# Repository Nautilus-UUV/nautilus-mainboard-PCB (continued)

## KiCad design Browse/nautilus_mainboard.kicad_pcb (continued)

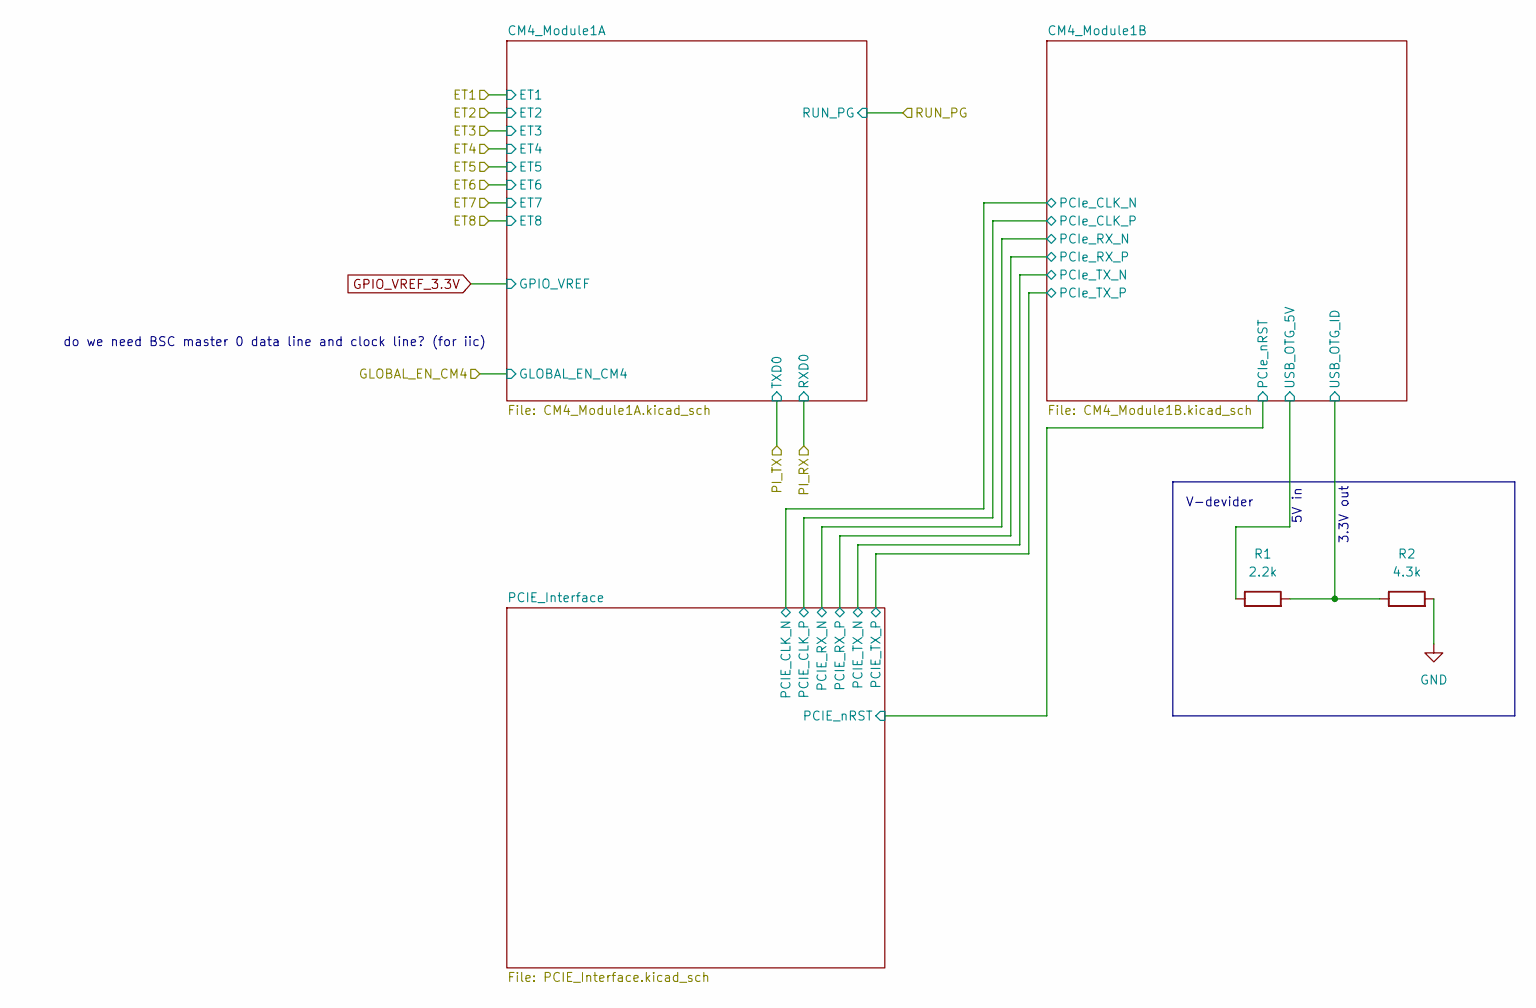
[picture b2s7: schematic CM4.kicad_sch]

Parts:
R1: 2.2k; R_0603_1608Metric; Tolerance 1 %; MPN 560112116098; LCSC CXXXXX
R2: 4.3k; R_0603_1608Metric; Tolerance 1 %; MPN 560112116141; LCSC CXXXXX

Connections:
/CM4/CM4_Module1B/USB_OTG_ID: R1.2, R2.1; also elsewhere on the board
GND: R2.2; also elsewhere on the board
USB_Out_5V: R1.1; also elsewhere on the board

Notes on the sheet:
do we need BSC master 0 data line and clock line? (for iic)
5V in
V-devider
3.3V out

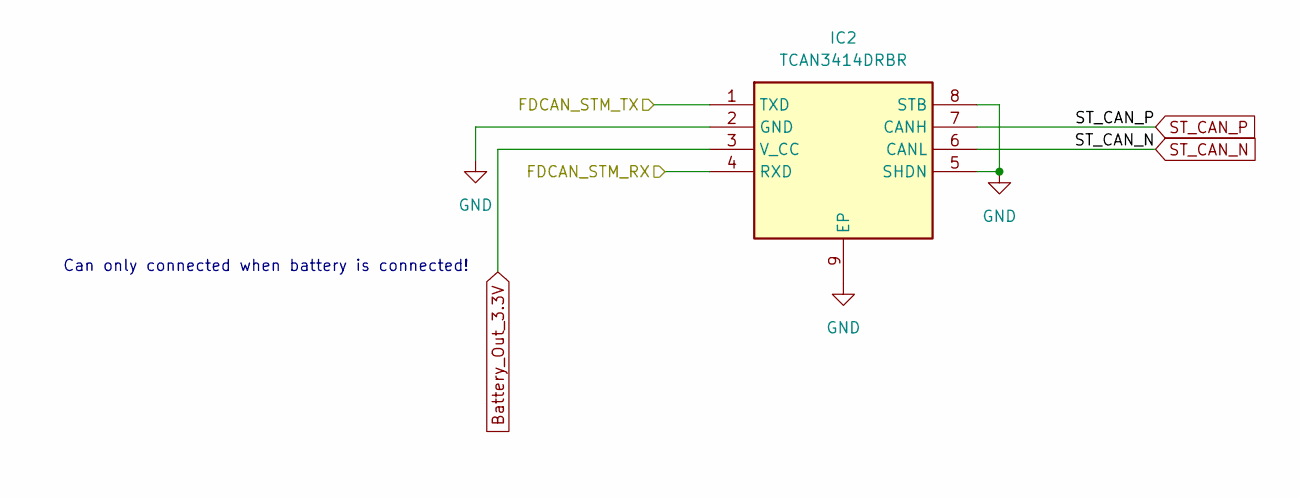
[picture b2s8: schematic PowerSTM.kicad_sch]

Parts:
IC2: TCAN3414DRBR; Mouser Part Number 595-TCAN3414DRBR

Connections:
/STM/PinoutSTM/CAN1_RX: IC2.4 (RXD); also elsewhere on the board
/STM/PinoutSTM/CAN1_TX: IC2.1 (TXD); also elsewhere on the board
GND: IC2.2 (GND), IC2.5 (SHDN), IC2.8 (STB), IC2.9 (EP); also elsewhere on the board
ST_CAN_N: IC2.6 (CANL); also elsewhere on the board
ST_CAN_P: IC2.7 (CANH); also elsewhere on the board

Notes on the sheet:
Can only connected when battery is connected!

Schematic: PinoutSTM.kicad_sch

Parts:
C8, C9: 4.7pF; C_0402_1005Metric; Voltage 50V; Tolerance ±0.25pF; MPN GRM1555C1H4R7CA01; LCSC C76946
C10, C15: 2.2pF; C_0402_1005Metric; Voltage 50V; Tolerance ±0.25pF; MPN GRM1555C1H2R2CA01; LCSC C85938
C11, C12, C13, C14, C17, C18, C19: 100nF; C_0603_1608Metric; Voltage 50V; Tolerance 10%; MPN 885012206095; LCSC CXXXXX
C16: 10uF; C_1210_3225Metric; Voltage 100V; Tolerance 10%; MPN GRM32EC72A106KE05; LCSC C5444485
EXTERNALFAN5V1: 0; R_0603_1608Metric; Tolerance 5%; MPN 560112116001; LCSC CXXXXX
IC1: STM32H7B0RBT6; LQFP-64_10x10mm_P0.5mm; Voltage 1.62V - 3.6V; Mouser Part Number 511-STM32H7B0RBT6
J1: FTSH-107-02-L-DV; FTSH-107-XX-YYY-DV; Mouser Part Number 200-FTSH10702LDV
J2: 61300211121; Wurth_Con_61300211121; MPN 61300211121
J4: Header male 1x05; PinHeader_1x05_P2.54mm_Vertical; MPN 22284054; LCSC C7501263
J5: 1792876; TerminalBlock_Phoenix_PT-1,5-3-5.0-H_1x03_P5.00mm_Horizontal; MPN 1792876; LCSC C976597
Q1: 50V; onsemi_Mosfet_BSS138; PARTREV 30 Jan 2018
R3: 1k; R_0603_1608Metric; Tolerance 1 %; MPN 560112116014; LCSC CXXXXX
R4: 10k; R_0603_1608Metric; Tolerance 1 %; MPN 560112116005; LCSC CXXXXX
SW1: Button Switch SPST-No; SW_PUSH_6mm; MPN B3F-1052; LCSC C87037
Y1: CC4V-T1A-32.768kHz-6pF-20PPM-TA-QC; CC4VT1A; Mouser Part Number 428-203148-MG02

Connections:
/CM4/CM4_Module1A/GPIO14: IC1.17 (PA3); also elsewhere on the board
/CM4/CM4_Module1A/GPIO15: IC1.16 (PA2); also elsewhere on the board
/CM4/GLOBAL_EN_CM4: IC1.11 (PC3); also elsewhere on the board
/CM4/RUN_PG: IC1.10 (PC2); also elsewhere on the board
/IMU/Pack1_SCL: IC1.61 (PB8); also elsewhere on the board
/IMU/Pack1_SDA: IC1.62 (PB9); also elsewhere on the board
/STM/PinoutSTM/CAN1_RX: IC1.43 (PA11); also elsewhere on the board
/STM/PinoutSTM/CAN1_TX: IC1.44 (PA12); also elsewhere on the board
/STM/PinoutSTM/Fan_ctrl: IC1.59 (PB7), R3.1
/STM/PinoutSTM/JTAG_ TDI: IC1.50 (PA15), J1.10
/STM/PinoutSTM/JTAG_TCK/SWCLK: IC1.49 (PA14), J1.6
/STM/PinoutSTM/JTAG_TDO/SWO: IC1.55 (PB3), J1.8
/STM/PinoutSTM/JTAG_TMS/SWDIO: IC1.45 (PA13), J1.4
/STM/PinoutSTM/SPI1_MISO: IC1.22 (PA6)
/STM/PinoutSTM/SPI1_MOSI: IC1.23 (PA7)
/STM/PinoutSTM/SPI1_NSS: IC1.20 (PA4)
/STM/PinoutSTM/SPI1_SCK: IC1.21 (PA5)
/STM/PinoutSTM/STM_BOOT0: IC1.60 (BOOT0), J4.4, R4.1
/STM/PinoutSTM/USART1_RX: IC1.42 (PA10), J1.13, J4.2
/STM/PinoutSTM/USART1_TX: IC1.41 (PA9), J1.14, J4.3
/STM/PinoutSTM/nRST: C19.1, IC1.7 (NRST), J1.12, SW1.1
BMI_IN_3.3V: C11.1, C12.1, C13.1, C14.1, C16.1, C17.1, C18.1, IC1.1 (VBAT), IC1.13 (VDDA), IC1.19 (VDD_1), IC1.32 (VDD_2), IC1.48 (VDD_3), IC1.64 (VDD_4), J1.3; also elsewhere on the board
Battery_Out_5V: EXTERNALFAN5V1.1, J5.1, J5.3; also elsewhere on the board
GND: C8.2, C9.2, C10.2, C11.2, C12.2, C13.2, C14.2, C15.2, C16.2, C17.2, C18.2, C19.2, IC1.12 (VSSA), IC1.18 (VSS_1), IC1.31 (VSS_2), IC1.47 (VSS_3), IC1.63 (VSS_4), J1.5, J1.7, J1.11, J2.2, J4.5, Q1.2, R4.2, SW1.2; also elsewhere on the board
unnamed: EXTERNALFAN5V1.2, J2.1
unnamed: C8.1, IC1.3 (PC14-OSC32_IN), Y1.2 (OUTPUT)
unnamed: C9.1, IC1.4 (PC15-OSC32_OUT), Y1.1
unnamed: C10.1, IC1.30 (VCAP_1)
unnamed: C15.1, IC1.46 (VCAP_2)
unnamed: J5.2, Q1.3
unnamed: Q1.1, R3.2
STM_Plug_3.3V: J4.1; also elsewhere on the board
STM_RX: IC1.15 (PA1); also elsewhere on the board
STM_TX: IC1.14 (PA0); also elsewhere on the board

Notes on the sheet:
Fan controller
I am a fan.
Connected to PB7
fan only active when battery is connected. Mby add an external power pin to externally power the fan for testing.
logic handled in power section
External interfaces
3v3 ext was first implemented here
- +

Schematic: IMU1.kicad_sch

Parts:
C43, C44: 100nF; C_0603_1608Metric; Voltage 50V; Tolerance 10%; MPN 885012206095; LCSC CXXXXX
R50, R51, R53: 0; R_0603_1608Metric; Tolerance 5%; MPN 560112116001; LCSC CXXXXX
U1: 262-BMI088; Bosch_IMU_BMI088; MPN 262-BMI088

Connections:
BMI_IN_3.3V: C43.2, C44.2, R53.1, U1.3 (VDD), U1.11 (VDDIO); also elsewhere on the board
GND: C43.1, C44.1, U1.2 (NC), U1.4 (GNDA), U1.6 (GNDIO), U1.10 (SDO2), U1.15 (SDO1); also elsewhere on the board
unnamed 130: R53.2, U1.7 (PS), U1.14 (CSB1); also elsewhere on the board
unnamed 131: R50.2, U1.8 (SCL/SCK); also elsewhere on the board
unnamed 132: R51.2, U1.9 (SDA/SDI); also elsewhere on the board

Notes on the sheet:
Accelerometer SD01 pin pulled to GND (0x18) SD01 pin pulled to VDDIO: (0x19) Gyroscope: SD02 pin pulled to GND: (0x68) SDO2 pin pulled to VDDIO: 0x69)
PB8 on STM
Acc: 0x18 Gyro: 0x68
PB9 on STM
PS -> 3.3V IIC CSB1 -> 3.3V NOT SPI

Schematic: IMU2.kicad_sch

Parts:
C45, C46: 100nF; C_0603_1608Metric; Voltage 50V; Tolerance 10%; MPN 885012206095; LCSC CXXXXX
R48, R49, R52: 0; R_0603_1608Metric; Tolerance 5%; MPN 560112116001; LCSC CXXXXX
U2: 262-BMI088; Bosch_IMU_BMI088; MPN 262-BMI088

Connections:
BMI_IN_3.3V: C45.2, C46.2, R52.1, U2.3 (VDD), U2.10 (SDO2), U2.11 (VDDIO), U2.15 (SDO1); also elsewhere on the board
GND: C45.1, C46.1, U2.2 (NC), U2.4 (GNDA), U2.6 (GNDIO); also elsewhere on the board
unnamed 133: R52.2, U2.7 (PS), U2.14 (CSB1); also elsewhere on the board
unnamed 134: R48.2, U2.8 (SCL/SCK); also elsewhere on the board
unnamed 135: R49.2, U2.9 (SDA/SDI); also elsewhere on the board

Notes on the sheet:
Acc: 0x19 Gyro: 0x69
PB8 on STM
PB9 on STM
Accelerometer SD01 pin pulled to GND (0x18) SD01 pin pulled to VDDIO: (0x19) Gyroscope: SD02 pin pulled to GND: (0x68) SDO2 pin pulled to VDDIO: 0x69)
PS -> 3.3V IIC CSB1 -> 3.3V NOT SPI

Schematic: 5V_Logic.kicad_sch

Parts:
C21, C22: 10uF; C_1210_3225Metric; Voltage 100V; Tolerance 10%; MPN GRM32EC72A106KE05; LCSC C5444485
C23, C24, C26: 100nF; C_0603_1608Metric; Voltage 50V; Tolerance 10%; MPN 885012206095; LCSC CXXXXX
C25: 330nF; C_0603_1608Metric; Voltage 50V; Tolerance 10%; MPN 885012206098; LCSC CXXXXX
C27: 47uF; C_0805_2012Metric; Voltage 10V; Tolerance 20%; MPN GRM21BR61A476ME15; LCSC C124129
IC3: TPS2121RUXT; TI_Switchover_TPS2121RUXT; Mouser Part Number 595-TPS2121RUXT
R16: 15.4k; R_0603_1608Metric; Tolerance 1 %; MPN 560112116105; LCSC CXXXXX
R17, R19: 4.99k; R_0603_1608Metric; Tolerance 1 %; MPN 560112116132; LCSC CXXXXX
R18: 22k; R_0603_1608Metric; Tolerance 1 %; MPN 560112116022; LCSC CXXXXX
R20: 20k; R_0603_1608Metric; Tolerance 1 %; MPN 560112116015; LCSC CXXXXX

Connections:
Battery_Out_5V: C21.1, C23.1, IC3.7 (IN1), R16.2; also elsewhere on the board
CM4_IN_5V: C26.1, C27.1, IC3.1 (OUT_1), IC3.8 (OUT_2); also elsewhere on the board
GND: C21.2, C22.2, C23.2, C24.2, C25.2, C26.2, C27.2, IC3.4 (OV2), IC3.5 (OV1), IC3.12 (GND), R17.1, R18.2, R19.1; also elsewhere on the board
unnamed: IC3.3 (CP2), R19.2, R20.1
unnamed: IC3.10 (ILIM), R18.1
unnamed: IC3.6 (PR1), R16.1, R17.2
unnamed: C25.1, IC3.11 (SS)
USB_Out_5V: C22.1, C24.1, IC3.2 (IN2), R20.2; also elsewhere on the board

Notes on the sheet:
for questions about wiring etc please consult the datasheet...
V-div to 1.2V when IN1 = 5V
if the USB-only cold start "disconnects" we can try to bump SS to 470nF instead of 330nF.
PR1 > CP2 -> IN1 has prio
100nF CLOSE
https://www.ti.com/lit/ds/symlink/tps2120.pdf?ts=1761678178328
V-div to 1V when IN2=5V
wrong caps. 100nf + 10myF

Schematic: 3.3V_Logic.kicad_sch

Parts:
C28, C29: 10uF; C_1210_3225Metric; Voltage 100V; Tolerance 10%; MPN GRM32EC72A106KE05; LCSC C5444485
C30, C31, C33: 100nF; C_0603_1608Metric; Voltage 50V; Tolerance 10%; MPN 885012206095; LCSC CXXXXX
C32: 330nF; C_0603_1608Metric; Voltage 50V; Tolerance 10%; MPN 885012206098; LCSC CXXXXX
C34: 47uF; C_0805_2012Metric; Voltage 10V; Tolerance 20%; MPN GRM21BR61A476ME15; LCSC C124129
IC5: TPS2121RUXT; TI_Switchover_TPS2121RUXT; Mouser Part Number 595-TPS2121RUXT
R21: 15.4k; R_0603_1608Metric; Tolerance 1 %; MPN 560112116105; LCSC CXXXXX
R22, R24: 4.99k; R_0603_1608Metric; Tolerance 1 %; MPN 560112116132; LCSC CXXXXX
R23: 68k; R_0603_1608Metric; Tolerance 1 %; MPN 560112116064; LCSC CXXXXX
R25: 20k; R_0603_1608Metric; Tolerance 1 %; MPN 560112116015; LCSC CXXXXX

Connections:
BMI_IN_3.3V: C33.1, C34.1, IC5.1 (OUT_1), IC5.8 (OUT_2); also elsewhere on the board
GND: C28.2, C29.2, C30.2, C31.2, C32.2, C33.2, C34.2, IC5.4 (OV2), IC5.5 (OV1), IC5.12 (GND), R22.1, R23.2, R24.1; also elsewhere on the board
unnamed: IC5.3 (CP2), R24.2, R25.1
unnamed: IC5.10 (ILIM), R23.1
unnamed: IC5.6 (PR1), R21.1, R22.2
unnamed: C32.1, IC5.11 (SS)
STM_Plug_3.3V: C29.1, C31.1, IC5.2 (IN2), R25.2; also elsewhere on the board

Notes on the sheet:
100nF CLOSE
V-div (same ratio as 5V)
if the USB-only cold start "disconnects" we can try to bump SS to 470nF instead of 330nF.
22 kΩ → ~4.55 A 39 kΩ → ~2.78 A 50 kΩ → ~2.25 A 56 kΩ → ~2.04 A 68 kΩ → ~1.72 A 100 kΩ → ~1.24 A
Pin 10: 68k leads to about 1.72A (should be enough for STM)
[R] = [kOhm] 65.2 / R^0.861
PR1 > CP2 -> IN1 has prio
SAME AS IN 5V

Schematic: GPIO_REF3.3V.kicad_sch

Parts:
C35, C36: 10uF; C_1210_3225Metric; Voltage 100V; Tolerance 10%; MPN GRM32EC72A106KE05; LCSC C5444485
C37, C38, C39, C40: 100nF; C_0603_1608Metric; Voltage 50V; Tolerance 10%; MPN 885012206095; LCSC CXXXXX
C41: 47uF; C_0805_2012Metric; Voltage 10V; Tolerance 20%; MPN GRM21BR61A476ME15; LCSC C124129
IC4: TPS2121RUXT; TI_Switchover_TPS2121RUXT; Mouser Part Number 595-TPS2121RUXT
R14: 15.4k; R_0603_1608Metric; Tolerance 1 %; MPN 560112116105; LCSC CXXXXX
R26, R28: 4.99k; R_0603_1608Metric; Tolerance 1 %; MPN 560112116132; LCSC CXXXXX
R27, R30: 100k; R_0603_1608Metric; Tolerance 1 %; MPN 560112116004; LCSC CXXXXX
R29: 20k; R_0603_1608Metric; Tolerance 1 %; MPN 560112116015; LCSC CXXXXX

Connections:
BMI_IN_3.3V: C35.1, C37.1, IC4.7 (IN1), R14.2; also elsewhere on the board
GND: C35.2, C36.2, C37.2, C38.2, C39.2, C40.2, C41.2, IC4.4 (OV2), IC4.5 (OV1), IC4.12 (GND), R26.1, R27.2, R28.1, R30.2; also elsewhere on the board
GPIO_VREF_3.3V: C40.1, C41.1, IC4.1 (OUT_1), IC4.8 (OUT_2), R30.1; also elsewhere on the board
unnamed: IC4.3 (CP2), R28.2, R29.1
unnamed: IC4.10 (ILIM), R27.1
unnamed: IC4.6 (PR1), R14.1, R26.2
unnamed: C39.1, IC4.11 (SS)

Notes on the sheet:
Pin SS (11): 100nF soft start cap more than enoug as virtually no load at all at vref
PR1 > CP2 -> IN1 has prio
[R] = [kOhm] 65.2 / R^0.861
100nF CLOSE
100kOhm pulldown so Vref is low if everything is off (not floating)
V-div (same ratio as 5V)
22 kΩ → ~4.55 A 39 kΩ → ~2.78 A 50 kΩ → ~2.25 A 56 kΩ → ~2.04 A 68 kΩ → ~1.72 A 100 kΩ → ~1.24 A
SAME AS IN 5V
Pin 10: 100kOhm leads to about 1.24A (absolute overkill)

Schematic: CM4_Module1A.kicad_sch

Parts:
C1, C2, C3, C4, C5, C6: 100nF; C_0603_1608Metric; Voltage 50V; Tolerance 10%; MPN 885012206095; LCSC CXXXXX
C7, C42: 1uF; C_0603_1608Metric; Voltage 50V; Tolerance 10%; MPN 885012206126; LCSC CXXXXX
C47: 10uF; C_1210_3225Metric; Voltage 100V; Tolerance 10%; MPN GRM32EC72A106KE05; LCSC C5444485
Module1: DF40C-100DS-0.4V(51); Con-Raspberry-Pi-4-Compute-Module; Part Description 100 Position Connector Receptacle, Cent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; LCSC lifecycle=Active; note=100-pin 0.4mm pi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
Q2: 50V; onsemi_Mosfet_BSS138; PARTREV 30 Jan 2018

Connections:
/CM4/CM4_Module1A/AIN0: Module1.96 (AnalogIP0)
/CM4/CM4_Module1A/AIN1: Module1.94 (AnalogIP1)
/CM4/CM4_Module1A/CM4_LED1/nPWR_LED: Module1.95 (nPI_LED_PWR); also elsewhere on the board
/CM4/CM4_Module1A/CM4_LED2/PI_nLED_Activity: Module1.21 (PI_nLED_Activity); also elsewhere on the board
/CM4/CM4_Module1A/ETH_LED_G: Module1.15 (Ethernet_nLED3(3.3v)); also elsewhere on the board
/CM4/CM4_Module1A/ETH_LED_Y: Module1.17 (Ethernet_nLED2(3.3v)); also elsewhere on the board
/CM4/CM4_Module1A/GLOBAL_EN: Module1.99 (Global_EN), Q2.3
/CM4/CM4_Module1A/GPIO2: Module1.58 (GPIO2)
/CM4/CM4_Module1A/GPIO3: Module1.56 (GPIO3)
/CM4/CM4_Module1A/GPIO4: Module1.54 (GPIO4)
/CM4/CM4_Module1A/GPIO5: Module1.34 (GPIO5)
/CM4/CM4_Module1A/GPIO6: Module1.30 (GPIO6)
/CM4/CM4_Module1A/GPIO7: Module1.37 (GPIO7)
/CM4/CM4_Module1A/GPIO8: Module1.39 (GPIO8)
/CM4/CM4_Module1A/GPIO9: Module1.40 (GPIO9)
/CM4/CM4_Module1A/GPIO10: Module1.44 (GPIO10)
/CM4/CM4_Module1A/GPIO11: Module1.38 (GPIO11)
/CM4/CM4_Module1A/GPIO12: Module1.31 (GPIO12)
/CM4/CM4_Module1A/GPIO13: Module1.28 (GPIO13)
/CM4/CM4_Module1A/GPIO14: Module1.55 (GPIO14); also elsewhere on the board
/CM4/CM4_Module1A/GPIO15: Module1.51 (GPIO15); also elsewhere on the board
/CM4/CM4_Module1A/GPIO16: Module1.29 (GPIO16)
/CM4/CM4_Module1A/GPIO17: Module1.50 (GPIO17)
/CM4/CM4_Module1A/GPIO18: Module1.49 (GPIO18)
/CM4/CM4_Module1A/GPIO19: Module1.26 (GPIO19)
/CM4/CM4_Module1A/GPIO20: Module1.27 (GPIO20)
/CM4/CM4_Module1A/GPIO21: Module1.25 (GPIO21)
/CM4/CM4_Module1A/GPIO22: Module1.46 (GPIO22)
/CM4/CM4_Module1A/GPIO23: Module1.47 (GPIO23)
/CM4/CM4_Module1A/GPIO24: Module1.45 (GPIO24)
/CM4/CM4_Module1A/GPIO25: Module1.41 (GPIO25)
/CM4/CM4_Module1A/GPIO26: Module1.24 (GPIO26)
/CM4/CM4_Module1A/GPIO27: Module1.48 (GPIO27)
/CM4/CM4_Module1A/TRD0_N: Module1.10 (Ethernet_Pair0_N); also elsewhere on the board
/CM4/CM4_Module1A/TRD0_P: Module1.12 (Ethernet_Pair0_P); also elsewhere on the board
/CM4/CM4_Module1A/TRD1_N: Module1.6 (Ethernet_Pair1_N); also elsewhere on the board
/CM4/CM4_Module1A/TRD1_P: Module1.4 (Ethernet_Pair1_P); also elsewhere on the board
/CM4/CM4_Module1A/TRD2_N: Module1.9 (Ethernet_Pair2_N); also elsewhere on the board
/CM4/CM4_Module1A/TRD2_P: Module1.11 (Ethernet_Pair2_P); also elsewhere on the board
/CM4/CM4_Module1A/TRD3_N: Module1.5 (Ethernet_Pair3_N); also elsewhere on the board
/CM4/CM4_Module1A/TRD3_P: Module1.3 (Ethernet_Pair3_P); also elsewhere on the board
/CM4/GLOBAL_EN_CM4: Q2.1; also elsewhere on the board
/CM4/RUN_PG: Module1.92 (RUN_PG); also elsewhere on the board
CM4_IN_5V: C1.1, C2.1, C3.1, C4.1, C5.1, C6.1, C7.1, C42.1, C47.1, Module1.77 (+5v_(Input)), Module1.79 (+5v_(Input)), Module1.81 (+5v_(Input)), Module1.83 (+5v_(Input)), Module1.85 (+5v_(Input)), Module1.87 (+5v_(Input)); also elsewhere on the board
GND: C1.2, C2.2, C3.2, C4.2, C5.2, C6.2, C7.2, C42.2, C47.2, Module1.1 (GND), Module1.2 (GND), Module1.7 (GND), Module1.8 (GND), Module1.13 (GND), Module1.14 (GND), Module1.22 (GND), Module1.23 (GND), Module1.32 (GND), Module1.33 (GND), Module1.42 (GND), Module1.43 (GND), Module1.52 (GND), Module1.53 (GND), Module1.59 (GND), Module1.60 (GND), Module1.65 (GND), Module1.66 (GND), Module1.71 (GND), Module1.74 (GND), Module1.89 (WL_nDisable), Module1.91 (BT_nDisable), Module1.98 (GND), Q2.2; also elsewhere on the board
GPIO_VREF_3.3V: Module1.78 (GPIO_VREF(1.8v/3.3v_Input)); also elsewhere on the board

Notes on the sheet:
Ethernet connection
GLOBAL_EN logic
Decoupling for CM4 5V inputs
N/A
connect Wlan to gnd if off, and leave floating for on. Please use a 2 pin connector here with a jumper cap. (has to be done)
GLOBAL_EN needs to be pulled low for >1ms after software shutdown.
Disable Wlan and Bluetooth?

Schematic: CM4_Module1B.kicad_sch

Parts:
C20: 4.7nF; C_0603_1608Metric; Voltage 50V; Tolerance 10%; MPN 885012206087; LCSC CXXXXX
D5: APHHS1005LCGCK; LED_0402_1005Metric; MPN APHHS1005LCGCK; LCSC C5354975
D6: SMF5.0A-TP; SMF50ATP; MPN 833-SMF5.0A-TP
J18: 179-UJ20CHC4SMTTR; CON_Samesky_CUI_UJ20-C-H-C-4-SMT-TR; PARTREV 1.0
Module1: DF40C-100DS-0.4V(51); Con-Raspberry-Pi-4-Compute-Module; Part Description 100 Position Connector Receptacle, Cent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; LCSC lifecycle=Active; note=100-pin 0.4mm pi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
R9: 2.7k; R_0603_1608Metric; Tolerance 1 %; MPN 560112116010; LCSC CXXXXX
R10, R12: 4.99k; R_0603_1608Metric; Tolerance 1 %; MPN 560112116132; LCSC CXXXXX
R11: 1M; R_0603_1608Metric; Tolerance 1 %; MPN 560112116074; LCSC CXXXXX
TPD4EUSB30DQAR3: IC_TPD4EUSB30DQAR; PARTREV F; LCSC C90627

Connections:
/CM4/CM4_Module1B/PCIe_CLK_N: Module1.112 (PCIe_CLK_N); also elsewhere on the board
/CM4/CM4_Module1B/PCIe_CLK_P: Module1.110 (PCIe_CLK_P); also elsewhere on the board
/CM4/CM4_Module1B/PCIe_RX_N: Module1.118 (PCIe_RX_N); also elsewhere on the board
/CM4/CM4_Module1B/PCIe_RX_P: Module1.116 (PCIe_RX_P); also elsewhere on the board
/CM4/CM4_Module1B/PCIe_TX_N: Module1.124 (PCIe_TX_N); also elsewhere on the board
/CM4/CM4_Module1B/PCIe_TX_P: Module1.122 (PCIe_TX_P); also elsewhere on the board
/CM4/CM4_Module1B/USB_D+: J18.A6 (DP1), J18.B6 (DP2), Module1.105 (USB2_P), TPD4EUSB30DQAR3.1, TPD4EUSB30DQAR3.2, TPD4EUSB30DQAR3.9 (Through_2), TPD4EUSB30DQAR3.10 (Through_1)
/CM4/CM4_Module1B/USB_D-: J18.A7 (DN1), J18.B7 (DN2), Module1.103 (USB2_N), TPD4EUSB30DQAR3.4, TPD4EUSB30DQAR3.5, TPD4EUSB30DQAR3.6 (Through_5), TPD4EUSB30DQAR3.7 (Through_4)
/CM4/CM4_Module1B/USB_OTG_ID: Module1.101 (USB_OTG_ID); also elsewhere on the board
/CM4/PCIE_Interface/PERST#: Module1.109 (PCIe_nRST); also elsewhere on the board
GND: C20.1, D6.2 (A), J18.A1_B12 (GND), J18.A12_B1 (GND), Module1.107 (GND), Module1.108 (GND), Module1.113 (GND), Module1.114 (GND), Module1.119 (GND), Module1.120 (GND), Module1.125 (GND), Module1.126 (GND), Module1.131 (GND), Module1.132 (GND), Module1.137 (GND), Module1.138 (GND), Module1.144 (GND), Module1.150 (GND), Module1.155 (GND), Module1.156 (GND), Module1.161 (GND), Module1.162 (GND), Module1.167 (GND), Module1.168 (GND), Module1.173 (GND), Module1.174 (GND), Module1.179 (GND), Module1.180 (GND), Module1.185 (GND), Module1.186 (GND), Module1.191 (GND), Module1.192 (GND), Module1.197 (GND), Module1.198 (GND), R9.2, R10.2, R11.2, R12.2, TPD4EUSB30DQAR3.3, TPD4EUSB30DQAR3.8; also elsewhere on the board
unnamed: C20.2, J18.SH1 (SHIELD), J18.SH2 (SHIELD), J18.SH3 (SHIELD), J18.SH4 (SHIELD), R11.1
unnamed: D5.1 (K), R9.1
unnamed: J18.A5 (CC1), R10.1
unnamed: J18.B5 (CC2), R12.1
USB_Out_5V: D5.2 (A), D6.1 (K), J18.A4_B9 (VBUS), J18.A9_B4 (VBUS); also elsewhere on the board

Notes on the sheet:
ESD/EMP protection for the USB
USB Connection for CM4
old usb port for reference.
Can be kept floating. if no usb is connected
reduce EMI
maybe RX and TX need to be switched
indicator LED :)
WIP, nRPI_BOOT? power only to certain parts? -> Diode (later) indication? (YES! LED)
Super important to not differ lengths or curve a lot with D+ and D-. Also should have same hole counts (vias) and same length.

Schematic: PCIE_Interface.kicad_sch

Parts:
CONFIG_1, CONFIG_2, CONFIG_3, CONFIG_4: 0; R_0603_1608Metric; Tolerance 5%; MPN 560112116001; LCSC CXXXXX
D8: APHHS1005LCGCK; LED_0402_1005Metric; MPN APHHS1005LCGCK; LCSC C5354975
J6: MDT275M02001; PCIE_MDT275M02001; Mouser Part Number 523-MDT275M02001
R13: 1k; R_0603_1608Metric; Tolerance 1 %; MPN 560112116014; LCSC CXXXXX

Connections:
/CM4/CM4_Module1B/PCIe_CLK_N: J6.53; also elsewhere on the board
/CM4/CM4_Module1B/PCIe_CLK_P: J6.55; also elsewhere on the board
/CM4/CM4_Module1B/PCIe_RX_N: J6.41; also elsewhere on the board
/CM4/CM4_Module1B/PCIe_RX_P: J6.43; also elsewhere on the board
/CM4/CM4_Module1B/PCIe_TX_N: J6.47; also elsewhere on the board
/CM4/CM4_Module1B/PCIe_TX_P: J6.49; also elsewhere on the board
/CM4/PCIE_Interface/CLKREQ#: J6.52
/CM4/PCIE_Interface/CONFIG_0: CONFIG_1.2, J6.21
/CM4/PCIE_Interface/CONFIG_1: CONFIG_2.2, J6.69
/CM4/PCIE_Interface/CONFIG_2: CONFIG_3.2, J6.75
/CM4/PCIE_Interface/CONFIG_3: CONFIG_4.2, J6.1
/CM4/PCIE_Interface/LED1_M2: D8.2 (A), J6.10, R13.1
/CM4/PCIE_Interface/NFG1: J6.56
/CM4/PCIE_Interface/NFG2: J6.58
/CM4/PCIE_Interface/PERST#: J6.50; also elsewhere on the board
/CM4/PCIE_Interface/PERn1: J6.29
/CM4/PCIE_Interface/PERn2: J6.17
/CM4/PCIE_Interface/PERn3: J6.5
/CM4/PCIE_Interface/PERp1: J6.31
/CM4/PCIE_Interface/PERp2: J6.19
/CM4/PCIE_Interface/PERp3: J6.7
/CM4/PCIE_Interface/PETn1: J6.35
/CM4/PCIE_Interface/PETn2: J6.23
/CM4/PCIE_Interface/PETn3: J6.11
/CM4/PCIE_Interface/PETp1: J6.37
/CM4/PCIE_Interface/PETp2: J6.25
/CM4/PCIE_Interface/PETp3: J6.13
/CM4/PCIE_Interface/PEWAKE#: J6.54
/CM4/PCIE_Interface/SUSCLK: J6.68
GND: CONFIG_1.1, CONFIG_2.1, CONFIG_3.1, CONFIG_4.1, D8.1 (K), J6.3, J6.9, J6.15, J6.27, J6.33, J6.39, J6.45, J6.51, J6.57, J6.71, J6.73, J6.76 (MP_1), J6.77 (MP_2); also elsewhere on the board

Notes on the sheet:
Led indicator

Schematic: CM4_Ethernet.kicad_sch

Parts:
D3: APHHS1005LSYCK/J3-PF; LED_0402_1005Metric; MPN APHHS1005LSYCK/J3-PF; LCSC C5354974
D4: APHHS1005LZGCK-V; LED_0402_1005Metric; MPN APHHS1005LZGCK-V; LCSC C5875752
R7, R8: 1k; R_0603_1608Metric; Tolerance 1 %; MPN 560112116014; LCSC CXXXXX
TPD4EUSB30DQAR1, TPD4EUSB30DQAR2: IC_TPD4EUSB30DQAR; PARTREV F; LCSC C90627

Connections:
/CM4/CM4_Module1A/ETH_LED_G: D4.1 (K); also elsewhere on the board
/CM4/CM4_Module1A/ETH_LED_Y: D3.1 (K); also elsewhere on the board
/CM4/CM4_Module1A/TRD0_N: TPD4EUSB30DQAR2.2, TPD4EUSB30DQAR2.9 (Through_2); also elsewhere on the board
/CM4/CM4_Module1A/TRD0_P: TPD4EUSB30DQAR2.1, TPD4EUSB30DQAR2.10 (Through_1); also elsewhere on the board
/CM4/CM4_Module1A/TRD1_N: TPD4EUSB30DQAR2.4, TPD4EUSB30DQAR2.7 (Through_4); also elsewhere on the board
/CM4/CM4_Module1A/TRD1_P: TPD4EUSB30DQAR2.5, TPD4EUSB30DQAR2.6 (Through_5); also elsewhere on the board
/CM4/CM4_Module1A/TRD2_N: TPD4EUSB30DQAR1.2, TPD4EUSB30DQAR1.9 (Through_2); also elsewhere on the board
/CM4/CM4_Module1A/TRD2_P: TPD4EUSB30DQAR1.1, TPD4EUSB30DQAR1.10 (Through_1); also elsewhere on the board
/CM4/CM4_Module1A/TRD3_N: TPD4EUSB30DQAR1.4, TPD4EUSB30DQAR1.7 (Through_4); also elsewhere on the board
/CM4/CM4_Module1A/TRD3_P: TPD4EUSB30DQAR1.5, TPD4EUSB30DQAR1.6 (Through_5); also elsewhere on the board
GND: TPD4EUSB30DQAR1.3, TPD4EUSB30DQAR1.8, TPD4EUSB30DQAR2.3, TPD4EUSB30DQAR2.8; also elsewhere on the board
unnamed: D3.2 (A), R8.1
unnamed: D4.2 (A), R7.1

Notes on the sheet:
Optimal: Yellow: 725 Ohm (3.3-1.85)/0.002
POE Protection
Optimal: Green: 325 Ohm (3.3-2.65)/0.002

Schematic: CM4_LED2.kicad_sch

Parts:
D2: APHHS1005LZGCK-V; LED_0402_1005Metric; MPN APHHS1005LZGCK-V; LCSC C5875752
R6: 1k; R_0603_1608Metric; Tolerance 1 %; MPN 560112116014; LCSC CXXXXX

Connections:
/CM4/CM4_Module1A/CM4_LED2/PI_nLED_Activity: R6.1; also elsewhere on the board
unnamed: D2.1 (K), R6.2

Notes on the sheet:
Simple Activity LED
Activity LED

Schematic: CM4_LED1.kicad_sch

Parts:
D1: APHHS1005LSECK/J3-PF; LED_0402_1005Metric; MPN APHHS1005LSECK/J3-PF
R5: 1k; R_0603_1608Metric; Tolerance 1 %; MPN 560112116014; LCSC CXXXXX
U3: Buffers & Line Driver; SOT65P210X110-5N; MPN 74LVC1G07SE-7; LCSC C67531

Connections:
/CM4/CM4_Module1A/CM4_LED1/nPWR_LED: U3.2; also elsewhere on the board
GND: U3.3 (GND); also elsewhere on the board
unnamed 100: D1.1 (K), R5.2; also elsewhere on the board
unnamed: R5.1, U3.4

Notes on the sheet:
Directly copied from the official CM4 io board (indicator LED for 3.3v)
then I would in theory compare internal voltage with internal voltage... so probably not...
only use when connected completely? not over usb???
<---
issue: will that logic work if I use USB vin only?

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
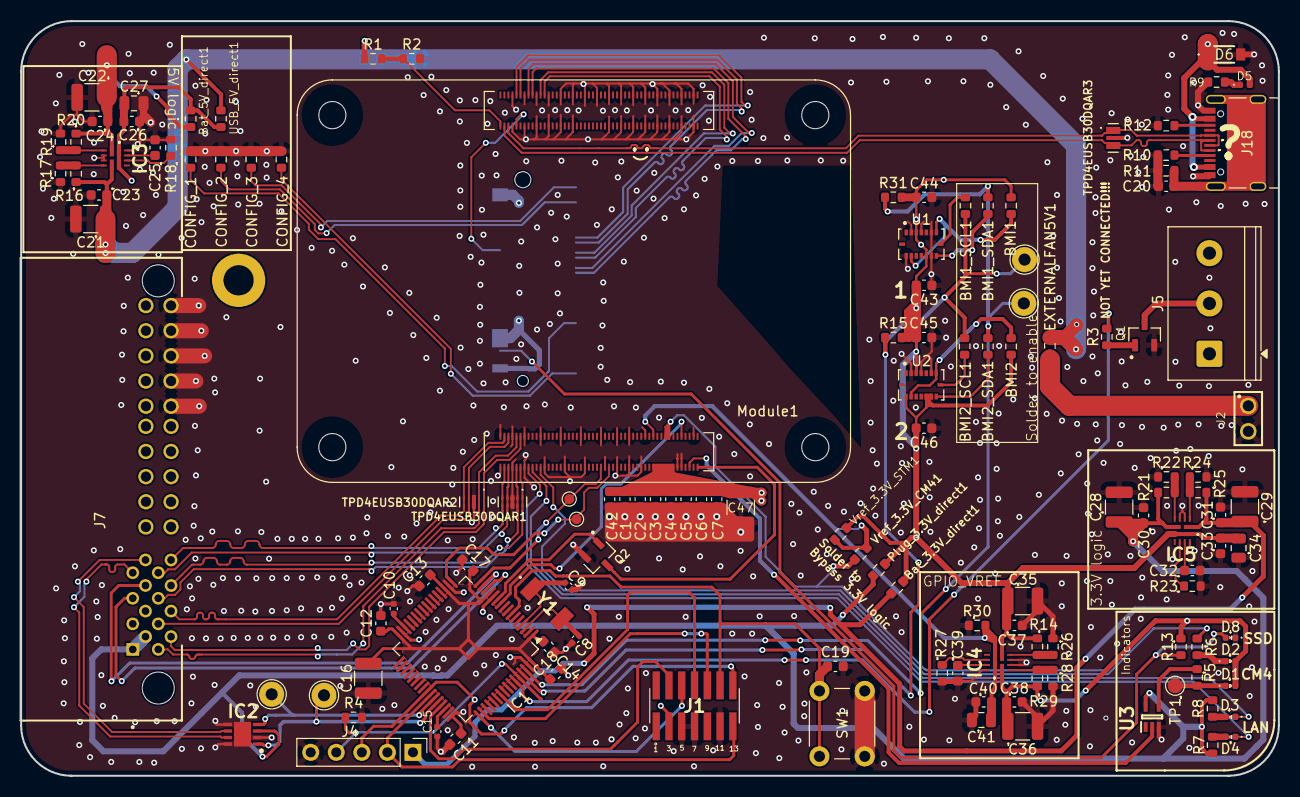
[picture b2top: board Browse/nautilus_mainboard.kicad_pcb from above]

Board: 4 copper layers, 125.0 x 75.0 mm, 132 parts (1 on the bottom side), 92 nets.

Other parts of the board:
BMI1, BMI1_SCL1, BMI1_SDA1, BMI2, BMI2_SCL1, BMI2_SDA1: 0; R_0603_1608Metric
TP1: Test Point; TestPoint_Pad_D1.5mm

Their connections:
/IMU/Pack1_SCL: BMI1_SCL1.1, BMI2_SCL1.1; also elsewhere on the board
/IMU/Pack1_SDA: BMI1_SDA1.1, BMI2_SDA1.1; also elsewhere on the board
BMI_IN_3.3V: BMI1.1, BMI2.1; also elsewhere on the board
unnamed 100: TP1.1; also elsewhere on the board
unnamed 130: BMI1.2; also elsewhere on the board
unnamed 131: BMI1_SCL1.2; also elsewhere on the board
unnamed 132: BMI1_SDA1.2; also elsewhere on the board
unnamed 133: BMI2.2; also elsewhere on the board
unnamed 134: BMI2_SCL1.2; also elsewhere on the board
unnamed 135: BMI2_SDA1.2; also elsewhere on the board

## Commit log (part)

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2025-09-19 Init
2025-09-20 test
2025-09-23 23.09.2025
2025-09-23 New Parts folder created, Additional pages for RTC created
2025-09-23 deleted backups and implemented gitignore
2025-10-14 Init2
2025-10-14 Added Indicator LED to CM4
2025-10-14 added gitignore, and did work on CM4
2025-10-15 started with the new STM integration
2025-10-16 Added other LED indicators, ethernet and connector (main connector to other pcb's)
2025-10-17 readded RX and TX, Corrected DZ_PATHS to be relative instead of absolute.
2025-10-17 Added usb connector
2025-10-18 added hirarchical pin
2025-10-18 Comments (+ new Connector?)
2025-10-21 Changed template of the sheet
2025-10-21 External interfaces
2025-10-21 WIFI connection changes PI
2025-10-21 beautyfie
2025-10-21 resolve project breaking merge conflict miss
2025-10-21 nothing
2025-10-21 Connected the Uart lines
2025-10-21 Implemented the entire can tranciever
2025-10-22 added more support for the ssd and fixed LED configuration
2025-10-26 multiple changes. fixed some mistakes, added jumper pins for wifi
2025-10-28 connector changes
2025-10-28 not working power distribution
2025-10-28 added caps
2025-10-28 power led
2025-10-28 added comment boxes
2025-10-28 simple changes
2025-10-28 scrivano datei (my thoughts written out)
2025-10-28 added fan Mosfet
2025-10-28 Added Power logic finally. (plus some comments on further improvements)
2025-10-29 tried to find some placements for power routing
2025-10-30 some PCB thoughts
2025-11-01 swapped vref and logic position
2025-11-01 checked the whole schematic with the datasheet, took notes/questions in the datasheet (pdf also uploaded)
2025-11-02 multiple changes to the differential pair for easier routing later.
2025-11-03 added Gyroscope and Accelerometer part (4x) over IIC
2025-11-04 connector with ssd
2025-11-04 new outline of board plus first traces
2025-11-04 ignore
2025-11-04 first tries with signal tracks
2025-11-10 routed the CAN
2025-11-10 fixed the can tranciever placement
2025-11-10 updated some diff pairs to be nicer
2025-11-10 cleaned up some schematic problems
2025-11-11 multiple chainges on PCB
2025-11-12 feat: kibot minimal setup
2025-11-12 fix: test easier config
2025-11-12 fix: run but don't fail on erc violations
2025-11-12 fix: check docs (https://kibot.readthedocs.io/en/latest/configuration/preflights/erc.html
2025-11-12 fix: disable checks
2025-11-12 fix: bump to kibot v2_k9
2025-11-12 feat: manual trigger
2025-11-12 fix: remove manual trigger, trigger on workflow change instead
2025-11-12 fix: use github maintained github action
2025-11-12 fix: make deploy separate job
2025-11-12 feat: test workflows from https://github.com/INTI-CMNB/kibot_variants_arduprog
2025-11-12 fix: revert to config workflow
2025-11-12 feat: improve to geenral config
2025-11-12 fix: keep running even on fail of ERC/DRC check
2025-11-12 fix: minimal config
2025-11-12 feat: add caching, fix: mkdir dir for Jekyll
2025-11-12 fix: race condition
2025-11-12 fix: removed unused files from the beginning (New_added_parts folder)
2025-11-12 feat: added README.md
2025-11-12 feat: go back to https://github.com/INTI-CMNB/kibot_variants_arduprog/blob/master/.github/workflows/kibot_quick_start.yml
2025-11-12 fix: add permission for private repo
2025-11-12 fix: add action: write permission
2025-11-12 chore: limit for quicker testing
2025-11-12 fix: specifically pass github_token
2025-11-13 fix: add pat token with permissions
2025-11-13 fix: no metadata permission exists
2025-11-13 fix: forgot to change PAT
2025-11-13 fix: add more outputs
2025-11-13 chore: for future uses of config, add index.html
2025-11-13 fix: try --quick-start with -D flag
2025-11-13 fix: just kibot --quick-start
2025-11-15 multiple rearrangements of the PCB
2025-11-15 feat: added multiple new routes to the PCB
2025-11-15 feat: new decoupling for STM chore: rethink the decoupling strategy for STM module (imo wayy too small)
2025-11-15 feat: nearly all connections done
2025-11-15 nearly complete with the PCB
2025-11-15 no substantial changes
2025-11-16 fix: widened the power tracks for 5V line
2025-11-16 added piezzo circuit and i2c line
2025-11-16 fix: adjusted copper to hole distance from 0.25mm to 0.2mm in order to meet the USB-C tolerances needed to use it.
2025-11-16 tented the vias(gnd) and routed the i2c and fan control path
2025-11-16 chore: remove DRC for pads being too close, or find a solution
2025-11-16 removed unused parts (piezzo) form pcb
2025-11-16 fix: adjusted clearance in order to pass DRC checks for BMI088
2025-11-16 chore: added a comment that piezzo buzzer wont be implemented right now
2025-11-16 chore: removed old hirarchical lables that were not being used anymore
2025-11-16 init with PDF
2025-11-16 fix: select types
2025-11-16 fix: removed ERC warnings, added missing overrides for ERC. Removed RX/TX for CM4, removed old power logic that was just there for legacy reasons.
2025-11-17 fix: remove token, repo public
2025-11-17 fix: test bare kibot --quick-start again
2025-11-17 fix: try -t navigate_results -t navigate_results_rb
2025-11-17 fix: cp nvigate page to index.html in root
2025-11-17 feat: generate index.html, add kikit_present
2025-11-17 fix: add navigation_results
2025-11-17 feat: deploy from gh-pages branch
2025-11-17 Initial gh-pages commit
2025-11-17 Deploying to gh-pages from @ Nautilus-UUV/nautilus-mainboard-PCB@41c404bf31bd09b274f764620f5ddef6d3709fa0 🚀
2025-11-17 Deploying to gh-pages from @ Nautilus-UUV/nautilus-mainboard-PCB@e643558b08d37d3a450dbfa2fadeff82d32b99a7 🚀
2025-11-17 added some testpoints
2025-11-17 Deploying to gh-pages from @ Nautilus-UUV/nautilus-mainboard-PCB@400426d46daeee198d0eea8645f966723a05ffff 🚀
2025-11-17 refilled all copper zones
2025-11-17 Deploying to gh-pages from @ Nautilus-UUV/nautilus-mainboard-PCB@ff07aeebf3c2c401dced3247772428d318509d16 🚀
2025-11-17 fix: add kiri
2025-11-17 Deploying to gh-pages from @ Nautilus-UUV/nautilus-mainboard-PCB@4ff1aa118bb53d619a79f793fe7c72f837f68351 🚀
2025-11-17 fix: remove config
2025-11-17 Deploying to gh-pages from @ Nautilus-UUV/nautilus-mainboard-PCB@c1f39ca1d3210f529365faafebe173d15c7f4bf8 🚀
2025-11-17 feat: custom config run instead, --quick-start fails because of inexisting In19.Cu layer
2025-11-17 Deploying to gh-pages from @ Nautilus-UUV/nautilus-mainboard-PCB@a8b0665ad2863a0a75eb02b0cc85feee954ca3bd 🚀
2025-11-17 refactor: remove basic_ from naming
2025-11-17 feat: layers: "all" for project independence
2025-11-17 Deploying to gh-pages from @ Nautilus-UUV/nautilus-mainboard-PCB@9864809d84881ecd1b7810f72565e7ed486200ab 🚀
2025-11-17 chore: add documentation on how to write .kibot.yaml
2025-11-18 chore: remove --quick-start documentation
2025-11-18 Deploying to gh-pages from @ Nautilus-UUV/nautilus-mainboard-PCB@de64703b928c8631e141fa49674662e67e202cb8 🚀
2025-11-18 Deploying to gh-pages from @ Nautilus-UUV/nautilus-mainboard-PCB@7e6573e0579e0dc2ccee4cf70d1ed7edfe61eb97 🚀
2025-11-18 added debugger pinout picture
2025-11-18 Deploying to gh-pages from @ Nautilus-UUV/nautilus-mainboard-PCB@b3f2008900590437af793175a127725f98172864 🚀
2025-11-18 Deploying to gh-pages from @ Nautilus-UUV/nautilus-mainboard-PCB@a8140ca9076140d9ca02896ef6eb584b07516917 🚀
2025-11-18 changed the piezzo buzzer
2025-11-18 Deploying to gh-pages from @ Nautilus-UUV/nautilus-mainboard-PCB@b7db83c6a38e7ed72f880de916f2e48939069e27 🚀
2025-11-18 added the diode
2025-11-18 Deploying to gh-pages from @ Nautilus-UUV/nautilus-mainboard-PCB@7631dd883fe8dd0df8a9e059de031ff5e1d7424d 🚀
2025-11-18 Symbal and naming changes
2025-11-18 updated a symbol
2025-11-18 Deploying to gh-pages from @ Nautilus-UUV/nautilus-mainboard-PCB@5df049b7efae0d903ad15eb9f94fe44d17db3268 🚀
2025-11-18 added lan bus
2025-11-18 Power changes
2025-11-18 Deploying to gh-pages from @ Nautilus-UUV/nautilus-mainboard-PCB@4372544f9d98c8c318df3aa79b1ddc615587ee00 🚀
2025-11-18 fix: 2 ERC errors fixed
2025-11-18 Deploying to gh-pages from @ Nautilus-UUV/nautilus-mainboard-PCB@f87e8fd5b4d00ad24387b205f01c25b4db3035ed 🚀
2025-11-18 chore: multiple cosmetic wiring changes
2025-11-18 Deploying to gh-pages from @ Nautilus-UUV/nautilus-mainboard-PCB@44ad8adb17f33e1aa4439bd10449a9ac7e221a1f 🚀
2025-11-18 chore: Many routing changes
2025-11-18 Deploying to gh-pages from @ Nautilus-UUV/nautilus-mainboard-PCB@a81f7ffbfc5f9b51f47d7f388c30fcea2673b9ea 🚀
2025-11-18 chore: more cleanup
2025-11-18 Deploying to gh-pages from @ Nautilus-UUV/nautilus-mainboard-PCB@2d3890115fd9d3c0bb909c9898aa64801bed9e67 🚀
2025-11-19 chore: added LED indicators for power and activity status, updated symbold, rerouted some things for better visibility
2025-11-19 Deploying to gh-pages from @ Nautilus-UUV/nautilus-mainboard-PCB@8b02e89ade7c168188296ba6f0516f3abec9166b 🚀
2025-11-19 chore: Loads of redoing stuff. Added a Changelog
2025-11-19 Empty PCB state
2025-11-19 Deploying to gh-pages from @ Nautilus-UUV/nautilus-mainboard-PCB@5b07cf6af03655ef9ddad269b1edd5eb03bfa75f 🚀
2025-11-19 Deploying to gh-pages from @ Nautilus-UUV/nautilus-mainboard-PCB@fedcd875819e048e6eb3ce13f9e0591eb16b9811 🚀
2025-11-19 Part placing 60% done
2025-11-19 Deploying to gh-pages from @ Nautilus-UUV/nautilus-mainboard-PCB@12c20cbf515726b93ab3378f8114ebfa0f38ccdc 🚀
2025-11-20 feat: use Nautilus-UUV/nautilus-kibot-action@main
2025-11-20 chore: add workflow_dispatch and test new action fixes
2025-11-20 Deploying to gh-pages from @ Nautilus-UUV/nautilus-mainboard-PCB@f91155f2bb2cd03d78cd6d0f924edf85e2bd4a1d 🚀
2025-11-20 Deploying to gh-pages from @ Nautilus-UUV/nautilus-mainboard-PCB@2b5265db7706a31505c0a0411337a4a604b5fb21 🚀
2025-11-23 chore: new testpoint symbols
2025-11-23 Deploying to gh-pages from @ Nautilus-UUV/nautilus-mainboard-PCB@e232027359a390dc54348e0f0abbe6a5df208f5c 🚀
2025-11-24 chore: routed many parts together. added testpoints
2025-11-24 Deploying to gh-pages from @ Nautilus-UUV/nautilus-mainboard-PCB@62d9beca31554f779583bfc3c938b3f82a581309 🚀
2025-11-25 chore: routed some parts, updated footprints, fixed unaligned footprints.
2025-11-25 Deploying to gh-pages from @ Nautilus-UUV/nautilus-mainboard-PCB@bceafb40b1bb594c1e1b2a2493b541123ce69437 🚀
2025-11-25 Deploying to gh-pages from @ Nautilus-UUV/nautilus-mainboard-PCB@5f5fdd9436d408a604bb268d740c0ac7ce1f5af5 🚀
2025-11-25 Deploying to gh-pages from @ Nautilus-UUV/nautilus-mainboard-PCB@5277c0e86ab227162151b0a74b3c344b92e8967f 🚀
2025-11-25 replaced the TSV diode for can with a new one
2025-11-25 Changed the crystal to a active oscillator
2025-11-25 added names
2025-11-25 Deploying to gh-pages from @ Nautilus-UUV/nautilus-mainboard-PCB@f1dd6ce1e57c066b805694b10777c719502cca87 🚀
2025-11-25 forgrot to add a 15pf cap and a 100n cap to the oscillator
2025-11-25 Deploying to gh-pages from @ Nautilus-UUV/nautilus-mainboard-PCB@4677f0d96ffb0bcbd05fb06bf37b6283fb7fe3ee 🚀
2025-11-25 fix: replaced 0402 components with 0603
2025-11-25 Deploying to gh-pages from @ Nautilus-UUV/nautilus-mainboard-PCB@a3368febe06499b73615c45b76cf3f9915566723 🚀
2025-11-25 Deploying to gh-pages from @ Nautilus-UUV/nautilus-mainboard-PCB@95dd30106b2062f6b52b0512e1ab1cb18de3091b 🚀
2025-11-25 added aris logo
2025-11-25 Deploying to gh-pages from @ Nautilus-UUV/nautilus-mainboard-PCB@6cba43b69b38d016a4625f92f8e1e4e823aff946 🚀
2025-11-25 feat: added logos
2025-11-25 Deploying to gh-pages from @ Nautilus-UUV/nautilus-mainboard-PCB@03be77246175febedc852bdb83cb4e2df1ae0c88 🚀
2025-11-25 chore: replaced 0 ohm with jumpers (not complete)
2025-11-25 Deploying to gh-pages from @ Nautilus-UUV/nautilus-mainboard-PCB@7cbe43864a66a110f5cd8f57d0dac694c5d0b0c8 🚀
2025-11-26 chore: routed the Jumpers (incomplete) fix: removed all leftover 0Ohm resistors
2025-11-26 Deploying to gh-pages from @ Nautilus-UUV/nautilus-mainboard-PCB@b731ca7531dd1e48b6b7a45790de08634e79c176 🚀
2025-11-28 chore: more routing + pin adjustments
2025-12-01 fix: removed unused pin for outside fan voltage supply
2025-12-02 feat: Review ready
2025-12-02 chore: added fun rotation to the cat, revoved eth logo
2025-12-02 pdf added
2025-12-03 Revise README for IMU and power supply details
    Updated IMU connection details and clarified power supply information.
2025-12-09 fix: minor changes, preparations for BOM and gerber, added Stitching
